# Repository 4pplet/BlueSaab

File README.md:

# BlueSaab

A CD-changer emulator that brings Bluetooth audio to classic SAAB cars.
BlueSaab plugs into the CD-changer connector, speaks the SAAB I-Bus CAN
protocol so the factory head unit believes a changer is present, and streams
music from your phone through the car's original audio path — steering-wheel
controls included.

**Supported cars:** SAAB 9-3 (1998–2002, Convertible –2003) and SAAB 9-5
(1998–2005; a 2006 Denso-nav 9-5 is confirmed working, other 2006+ cars are
unverified — see the 9-5 notes). The 2003+ 9-3 Sport Sedan uses a different
(GMLAN) architecture and is not supported.

## Current hardware: v6.1 (STM32 + RN52)

- STM32F103RB MCU running mbed OS 2 (vendored), Microchip RN52 Bluetooth 3.0
  audio module, CAN at 47.619 kbit/s
- Firmware: **v6.1.1** is the latest release
  ([download](https://github.com/4pplet/BlueSaab/releases)); this repo's root
  is the firmware source, currently **v6.1.7** — unreleased, pending in-car
  validation (see [CHANGELOG.md](CHANGELOG.md))
- Board design files in [HARDWARE/](HARDWARE/README.md)
- The RN52 went end-of-life in 2024 and Arm retired Mbed in 2026, so v6
  hardware is frozen: existing units keep working (modern iPhones/Androids
  stream to it fine over A2DP) and still get firmware improvements, while
  the main effort is the successor below.

## Using it

See **[docs/USAGE_v6.md](docs/USAGE_v6.md)** — pairing procedure, full
button map, debug serial console, troubleshooting. Short version: select the
CD-changer source, press preset **1**, pair with "BlueSaab v6" on your phone.

## The successor (in design)

A spiritual successor is being designed around a single **ESP32**: same
in-car interface, same connector, plus multi-device pairing/swap and a
sub-100 µA parked power target. Design docs:

- [docs/SUCCESSOR_HARDWARE_OPTIONS.md](docs/SUCCESSOR_HARDWARE_OPTIONS.md) —
  hardware evaluation and decisions
- [docs/IBUS_PROTOCOL.md](docs/IBUS_PROTOCOL.md) — the I-Bus CDC protocol
  (the spec any new firmware must honor)
- [docs/SAAB_9-5_NOTES.md](docs/SAAB_9-5_NOTES.md) — 9-5 bus research and
  model-specific quirks
- [docs/RELATED_PROJECTS.md](docs/RELATED_PROJECTS.md) — lineage,
  competitors, and how 2006+ cars are handled
- [TODO.md](TODO.md) — the roadmap

## Building v6 firmware

See [docs/BUILD_v6.md](docs/BUILD_v6.md) (toolchain, CI, release process) and
[docs/FLASHING_v6_HOWTO.md](docs/FLASHING_v6_HOWTO.md).

## Credits & history

- Hardware design: Seth Evans (bluesaab.blogspot.com)
- Initial code: Seth Evans and Emil Fors
- v6 firmware: Girts Linde and Karlis Veilands
- I-Bus protocol research: Tomi Liljemark
  ([archived](http://web.archive.org/web/20250122150340/http://pikkupossu.1g.fi/tomi/projects/i-bus/i-bus.html))
- RN52 handling based on RN52lib by Tim Otto
- Predecessor codebase: [SAAB-CDC](https://github.com/kveilands/SAAB-CDC)
  (Arduino generation)

## License

GPL-3.0-or-later — see [LICENSE](LICENSE).

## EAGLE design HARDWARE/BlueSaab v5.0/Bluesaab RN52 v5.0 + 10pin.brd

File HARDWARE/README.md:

# BlueSaab Hardware

Board design files for the BlueSaab CD changer emulator — a device that plugs into
the CD changer connector of older SAAB cars (9-3/9-5 with I-Bus) and streams
Bluetooth audio via a Microchip RN52 module.

## Contents

| File | Description |
| --- | --- |
| `BlueSaab_v6.PDF` | Schematic for hardware v6 (targeted by all 6.1.x firmware) |
| `BOM_PartType-BlueSaab_v6_1_1.csv` | Bill of materials for v6.1.1 |
| `BlueSaab v5.0/` | Full v5.0 design: Eagle `.sch`/`.brd` sources plus PDF exports ("RN52 v5.0 + 10pin"); the `.zip` inside holds the v5.0 **Gerbers** |
| `Hardware - Installing BlueSAAB module in cars without CDC provisioning cable.pdf` | Install guide for cars lacking the CDC pre-wiring |
| `Screen_Shot_2016-10-26_at_09.png` | Reference screenshot (2016) |

## v6 architecture (current)

- **MCU:** STM32F103RB (Cortex-M3), programmed via the ROM serial bootloader
  on the FTDI header (primary) or SWD — see
  [docs/FLASHING_v6_HOWTO.md](../docs/FLASHING_v6_HOWTO.md)
- **Bluetooth:** Microchip RN52 (Bluetooth 3.0 Classic, A2DP/AVRCP)
- **CAN:** SAAB I-Bus at 47.619 kbps, SN65HVD234 transceiver
- **Power:** LM1117-3.3 linear regulator from the CDC connector's 12 V
  (battery-fed, not ignition-switched)
- **Enclosure:** BUD Industries CU-3242

## Headers and connectors (from the schematic)

| Header | Pins | Use |
| --- | --- | --- |
| CDC connector P1 (TE 827229-1) | 6 = 12 V, 12 = GND, 11/5 = CAN H/L, 7/2 = R±, 8/3 = L± | The car |
| FTDI (6-pin) | 1 = GND (black), 3 = 5 V in (red), 4 = USART1_RX (orange), 5 = USART1_TX (yellow) | Flashing (ROM bootloader) |
| UART2 (2-pin) | 1 = TX (PA2), 2 = RX (PA3) — **no GND** | Debug console, 115200 8N1, 3.3 V only |
| UART3 (2-pin) | 1 → RN52 RX, 2 ← RN52 TX — **no GND** | Direct RN52 UART (DFU) |
| EXT VCC (2-pin) | 1 = 3.3 V, 2 = GND | Handy ground for the UART headers |
| SWD (10-pin 1.27 mm) | 1 = VCC sense, 2 = SWDIO, 4 = SWCLK, 3/5/9 = GND, 10 = RESET | ST-Link |
| MicroUSB J1 | 5 V in via diode D2; D+/D- to PA11/PA12 (unused by firmware) | Bench power only |

## Known issues / status

- The **RN52 is end-of-life**: Microchip PCN MFOL-01KSIK286 (April 2024),
  last shipment June 2024, recommended replacement BM83. Only broker stock
  remains. It still works fine with modern phones (A2DP/SBC over Bluetooth
  Classic), but no new v6 boards can be built — hence the ESP32 successor.
- Editable sources (Eagle) exist only for v5.0; v6 is PDF + BOM only. If the v6 CAD
  files can be recovered, add them here.
- Parked current draw has never been measured (estimated 15–30 mA). The
  LM1117 alone draws ~5–10 mA quiescent.

## Interim mod: inline power switch

Until the sleep firmware exists (planned for 6.2.0 — see TODO.md), the unit
draws power continuously — enough to trouble a battery over weeks of
parking, hence the unplug-when-unused ritual. A cleaner interim fix: splice a
small automotive toggle switch into the **12 V wire (connector pin 6)** near
the plug.

- Switching only 12 V is electrically clean: an unpowered CAN transceiver is
  high-impedance on the bus, the silent audio stage is harmless, and the car
  simply sees "no changer" — identical to unplugging.
- Any small switch rated for ≥ 1 A at 12 V works (the unit's peak draw is
  unmeasured but far below that). No enclosure or board changes.
- Flip it on with the ignition on and the unit boots onto a live bus. Use
  firmware 6.1.7 or later: 6.1.6 could occasionally hang at such a boot, and
  6.1.1 is fine.
- Caveat: manual = forgettable in both directions (drain anyway / "why is
  Bluetooth dead?"). The planned sleep firmware makes it largely obsolete.

## Low-Iq regulator mod — read before soldering

A lower-quiescent regulator only pays off together with sleep firmware, and
it is **not a drop-in swap**. See the "Optional hardware mod" section in
[TODO.md](../TODO.md). In short:

- Low-Iq automotive LDOs like the MCP1792 use a VIN–GND–VOUT SOT-223 pinout
  with the tab on GND, while the LM1117 is GND–VOUT–VIN with the tab on VOUT.
  Soldered onto the LM1117 footprint, the MCP1792 gets 12 V on its output
  and is destroyed.
- The MCP1792 is also a 100 mA part — measure the peak current first.

## Planned successor direction

Replace both the STM32 and the RN52 with a single **ESP32** (the original ESP32 —
not S3/C3, which lack Bluetooth Classic):

- A2DP sink + AVRCP supported in the free ESP-IDF
- Built-in CAN (TWAI) controller — only an external transceiver needed, and
  TWAI hits the I-Bus 47.619 kbps rate exactly
- Collapses the board to one module + transceiver + power + connector

See [docs/SUCCESSOR_HARDWARE_OPTIONS.md](../docs/SUCCESSOR_HARDWARE_OPTIONS.md)
and the repo root [TODO.md](../TODO.md).

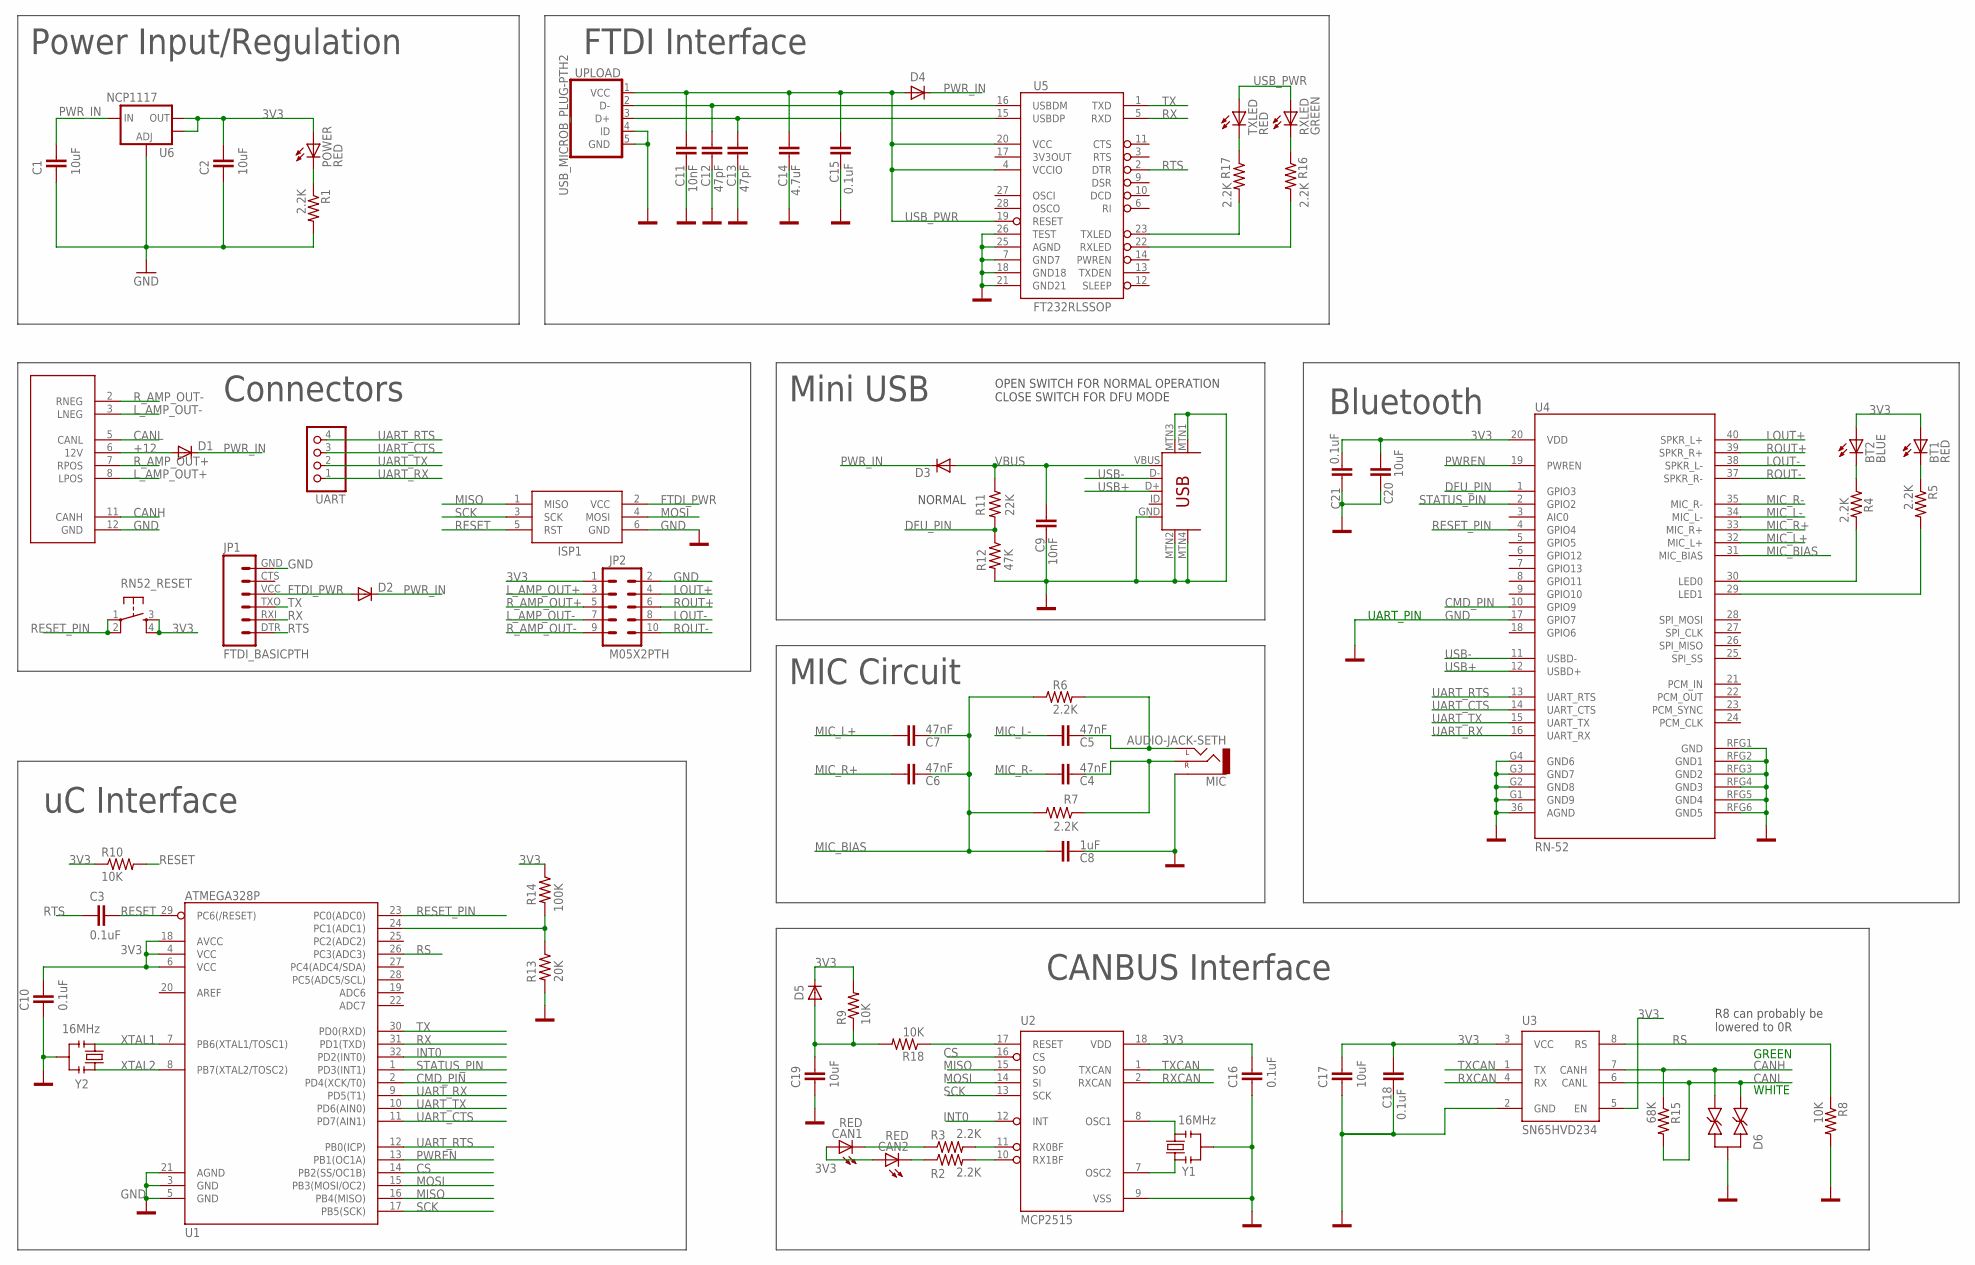
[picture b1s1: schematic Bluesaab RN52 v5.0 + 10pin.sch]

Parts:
BT1: RED; SML1206
BT2: BLUE; SML1206
C1, C2, C17, C19, C20: 10uF; C0805K
C3, C10, C15, C16, C18, C21: 0.1uF; C0805K
C4, C5, C6, C7: 47nF; C0805K
C8: 1uF; C0805K
C9, C11: 10nF; C0805K
C12, C13: 47pF; C0805K
C14: 4.7uF; C0805K
CAN1, CAN2: RED; SML1206
D1, D2, D3, D4, D5: DIODE-SCHOTTKY_; SOD123
D6: DIODE-ARRAY; SOT23
ISP1: AVRISP-6; AVRISP
JP1: FTDI_BASICPTH; FTDI_BASIC
JP2: M05X2PTH; AVR_ICSP
MIC: AUDIO-JACK-SETH; AUDIO-JACK-3.5MM-SMD-SETH
POWER: RED; SML1206
R1, R2, R3, R4, R5, R6, R7, R16, R17: 2.2K; R0805
R8, R9, R10, R18: 10K; R0805
R11: 22K; R0805
R12: 47K; R0805
R13: 20K; R0805
R14: 100K; R0805
R15: 68K; R0805
RN52_FIRMWARE: USB-MINIB-5PIN; USB-MINIB
RN52_RESET: TAC_SWITCH; TACTILE_SWITCH_SMD_6MM
RXLED: GREEN; SML1206
TXLED: RED; SML1206
U1: ATMEGA328P; TQFP32-08
U2: MCP2515; SO18L
U3: SN65HVD234; SO8
U4: RN-52
U5: FT232RLSSOP; SSOP28DB
U6: NCP1117; SOT223
U$5: 827229-1
UART: PINHD-1X4; 1X04
UPLOAD: USB_MICROB_PLUG-PTH2; MICRO-B-TH
Y1, Y2: 16MHz; RESONATOR-SMD

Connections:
3V3: BT1.A, BT2.A, C2.2, C10.2, C16.2, C17.2, C18.1, C20.1, C21.2, CAN1.A, CAN2.A, D5.C, JP2.1, POWER.A, R9.2, R10.1, R14.1, RN52_RESET.3, RN52_RESET.4, U1.4 (VCC), U1.6 (VCC), U1.18 (AVCC), U2.18 (VDD), U3.3 (VCC), U3.5 (EN), U4.20 (VDD), U6.2 (OUT), U6.4 (OUT)
+12: D1.A, U$5.6 (12V)
CANH: D6.2, R15.1, U3.7 (CANH), U$5.11 (CANH)
CANL: D6.1, R15.2, U3.6 (CANL), U$5.5 (CANL)
CMD_PIN: U1.2 (PD4(XCK/T0)), U4.10 (GPIO9)
CS: U1.14 (PB2(SS/OC1B)), U2.16 (CS)
DFU_PIN: R11.2, R12.1, U4.1 (GPIO3)
FTDI_PWR: D2.A, ISP1.2 (VCC), JP1.VCC (4)
GND: C1.1, C2.1, C8.1, C9.1, C10.1, C11.1, C12.1, C13.1, C14.1, C15.2, C16.1, C17.1, C18.2, C19.1, C20.2, C21.1, D6.3, ISP1.6 (GND), JP1.GND (6), JP2.2, MIC.SLEEVE, R1.2, R8.2, R12.2, R13.2, RN52_FIRMWARE.GND, RN52_FIRMWARE.MTN1 (MTN2), RN52_FIRMWARE.MTN2 (MTN3), RN52_FIRMWARE.MTN3 (MTN1), RN52_FIRMWARE.MTN4, U1.3 (GND), U1.5 (GND), U1.21 (AGND), U2.9 (VSS), U3.2 (GND), U4.17 (GPIO7), U4.36 (AGND), U4.G1 (GND9), U4.G2 (GND8), U4.G3 (GND7), U4.G4 (GND6), U4.RFG1 (GND), U4.RFG2 (GND1), U4.RFG3 (GND2), U4.RFG4 (GND3), U4.RFG5 (GND4), U4.RFG6 (GND5), U5.7 (GND7), U5.18 (GND18), U5.21 (GND21), U5.25 (AGND), U5.26 (TEST), U6.1 (ADJ), U$5.12 (GND), UPLOAD.4 (ID), UPLOAD.5 (GND), Y1.2, Y2.2
INT0: U1.32 (PD2(INT0)), U2.12 (INT)
LOUT+: JP2.4, U4.40 (SPKR_L+)
LOUT-: JP2.8, U4.38 (SPKR_L-)
L_AMP_OUT+: JP2.3, U$5.8 (LPOS)
L_AMP_OUT-: JP2.7, U$5.3 (LNEG)
MIC_BIAS: C6.1, C7.1, C8.2, R6.1, R7.2, U4.31 (MIC_BIAS)
MIC_L+: C7.2, U4.32 (MIC_L+)
MIC_L-: C5.1, U4.34 (MIC_L-)
MIC_R+: C6.2, U4.33 (MIC_R+)
MIC_R-: C4.1, U4.35 (MIC_R-)
MISO: ISP1.1 (MISO), U1.16 (PB4(MISO)), U2.15 (SO)
MOSI: ISP1.4 (MOSI), U1.15 (PB3(MOSI/OC2)), U2.14 (SI)
unnamed: R16.2, U5.22 (RXLED)
unnamed: U2.8 (OSC1), Y1.3
unnamed: U2.7 (OSC2), Y1.1
unnamed: BT2.C, R4.1
unnamed: BT1.C, R5.1
unnamed: R18.1, U2.17 (RESET)
unnamed: R13.1, R14.2, U1.24 (PC1(ADC1))
unnamed: R17.2, U5.23 (TXLED)
unnamed: R16.1, RXLED.C
unnamed: CAN1.C, R3.1
unnamed: R17.1, TXLED.C
unnamed: CAN2.C, R2.1
unnamed: POWER.C, R1.1
unnamed: R3.2, U2.11 (RX0BF)
unnamed: C4.2, MIC.RING (RIGHT), R7.1
unnamed: C5.2, MIC.TIP (LEFT), R6.2
unnamed: R5.2, U4.29 (LED1)
unnamed: R4.2, U4.30 (LED0)
unnamed: R2.2, U2.10 (RX1BF)
unnamed: C19.2, D5.A, R9.1, R18.2
PWREN: U1.13 (PB1(OC1A)), U4.19 (PWREN)
PWR_IN: C1.2, D1.C, D2.C, D3.C, D4.C, U6.3 (IN)
RESET: C3.2, ISP1.5 (RST), R10.2, U1.29 (PC6(/RESET))
RESET_PIN: RN52_RESET.1, RN52_RESET.2, U1.23 (PC0(ADC0)), U4.4 (GPIO4)
ROUT+: JP2.6, U4.39 (SPKR_R+)
ROUT-: JP2.10, U4.37 (SPKR_R-)
RS: R8.1, U1.26 (PC3(ADC3)), U3.8 (RS)
RTS: C3.1, JP1.DTR (1), U5.2 (DTR)
RX: JP1.RXI (2), U1.31 (PD1(TXD)), U5.5 (RXD)
RXCAN: U2.2 (RXCAN), U3.4 (RX)
R_AMP_OUT+: JP2.5, U$5.7 (RPOS)
R_AMP_OUT-: JP2.9, U$5.2 (RNEG)
SCK: ISP1.3 (SCK), U1.17 (PB5(SCK)), U2.13 (SCK)
STATUS_PIN: U1.1 (PD3(INT1)), U4.2 (GPIO2)
TX: JP1.TXO (3), U1.30 (PD0(RXD)), U5.1 (TXD)
TXCAN: U2.1 (TXCAN), U3.1 (TX)
UART_CTS: U1.11 (PD7(AIN1)), U4.14 (UART_CTS), UART.3
UART_RTS: U1.12 (PB0(ICP)), U4.13 (UART_RTS), UART.4
UART_RX: U1.9 (PD5(T1)), U4.16 (UART_RX), UART.1
UART_TX: U1.10 (PD6(AIN0)), U4.15 (UART_TX), UART.2
USB+: RN52_FIRMWARE.D+, U4.12 (USBD+)
USB-: RN52_FIRMWARE.D-, U4.11 (USBD-)
USBDM: C12.2, U5.16 (USBDM), UPLOAD.2 (D-)
USBDP: C13.2, U5.15 (USBDP), UPLOAD.3 (D+)
USB_PWR: C11.2, C14.2, C15.1, D4.A, RXLED.A, TXLED.A, U5.4 (VCCIO), U5.19 (RESET), U5.20 (VCC), UPLOAD.1 (VCC)
VBUS: C9.2, D3.A, R11.1, RN52_FIRMWARE.VBUS
XTAL1: U1.7 (PB6(XTAL1/TOSC1)), Y2.1
XTAL2: U1.8 (PB7(XTAL2/TOSC2)), Y2.3

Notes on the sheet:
GREEN
WHITE
CANBUS Interface
Connectors
Power Input/Regulation
Bluetooth
Mini USB
MIC Circuit
NORMAL
OPEN SWITCH FOR NORMAL OPERATION CLOSE SWITCH FOR DFU MODE
uC Interface
UART_PIN
FTDI Interface
R8 can probably be lowered to 0R

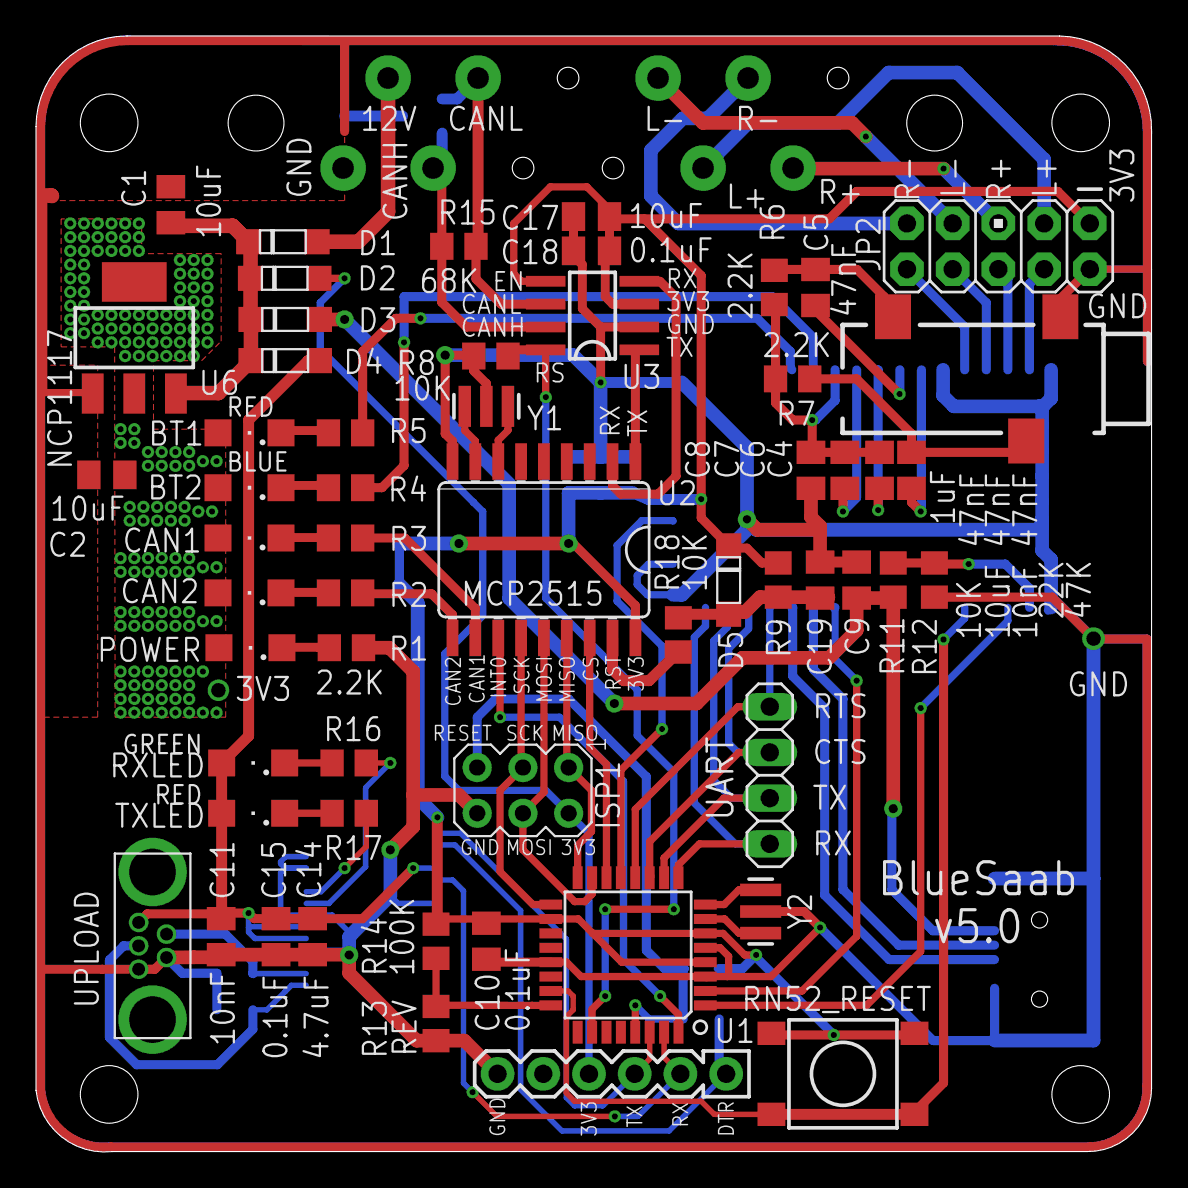
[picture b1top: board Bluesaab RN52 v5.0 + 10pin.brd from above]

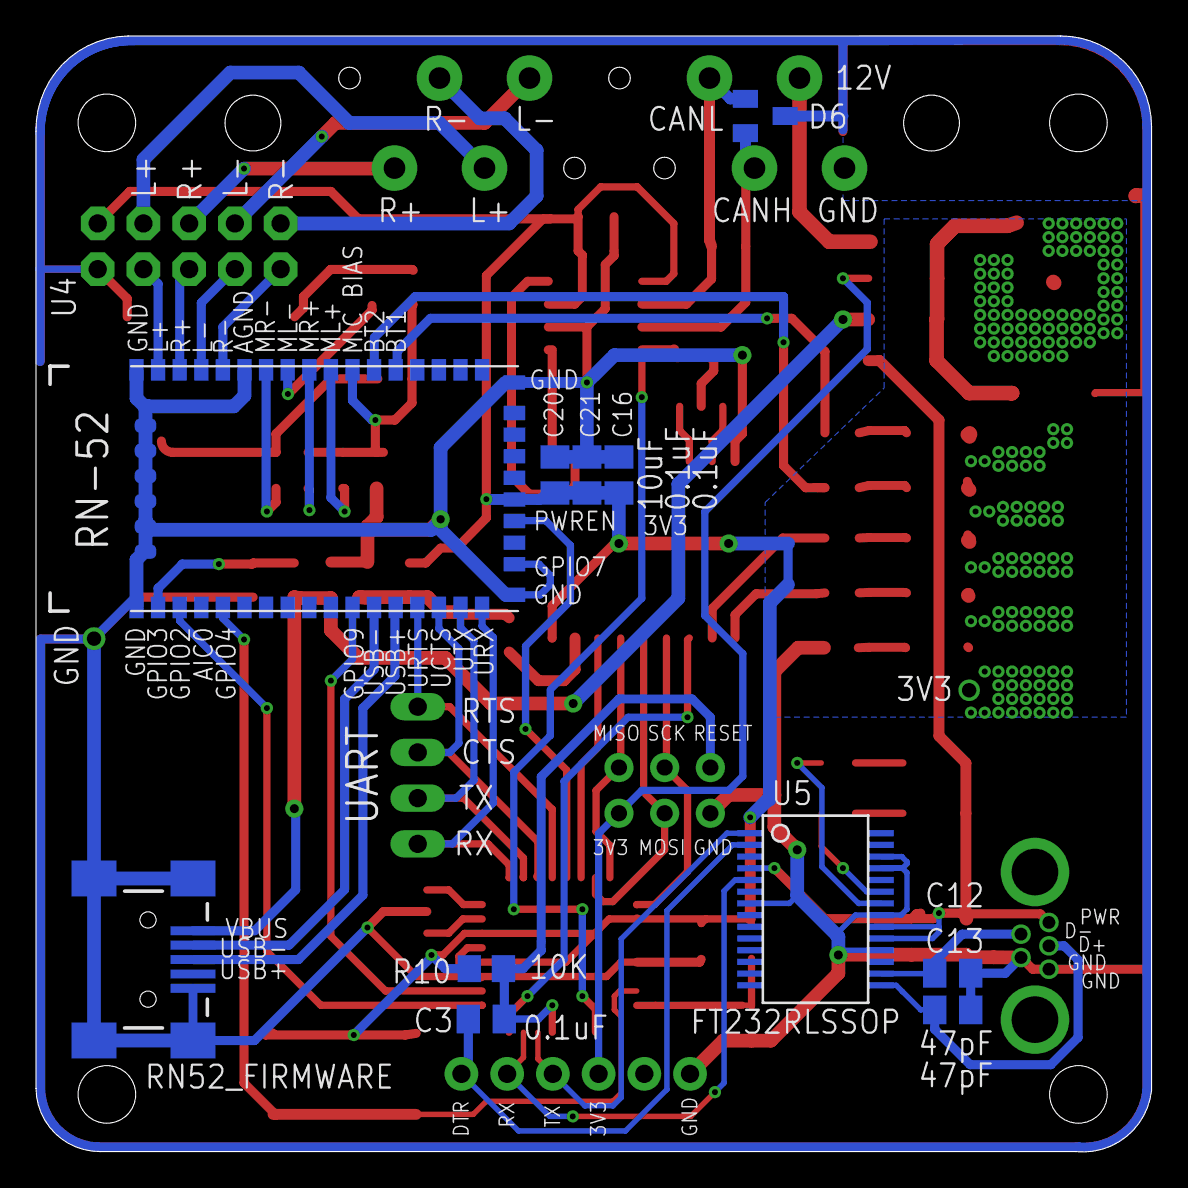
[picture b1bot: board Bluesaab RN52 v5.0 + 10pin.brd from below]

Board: 2 copper layers, 62.0 x 62.0 mm, 69 parts (11 on the bottom side), 69 nets.

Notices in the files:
parts and their libraries:
SparkFun-DigitalIC: Licensing: CC v3.0 Share-Alike You are welcome to use this library for commercial purposes.
SparkFun-RF: Licensing: Creative Commons ShareAlike 4.0 International - https://creativecommons.org/licenses/by-sa/4.0
